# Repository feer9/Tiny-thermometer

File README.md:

# Tiny-thermomether

This project is mostly a recopilation of other projects I've found on various pages.  
I've just joined them at my personal taste, so I'll let the link to those projects below.  

## Parts used

+ ATtiny85
+ SSD1306 128x32 OLED I2C Display
+ DHT11 temperature and humidity sensor
+ DS18B20 water temperature sensor

## Electrical connection

ATtiny85  | PCB                   | Debug
--------- | --------------------- | --------
PB0       | Display SDA           | MOSI
PB1       | Push button           | MISO
PB2       | Display SCL           | CLK
PB3       | DHT11 (pin 2)         |
PB4       | DS18B20 (yellow wire) |
PB5       | N/C                   | RST

The sensors data lines have a 4.7K PullUp resistor.  
The push button have a 10K resistor.  
The I2C bus have a 10K PullUp resistor, both in SDA and SCL.

## Compilation and flashing

I've only tested it with avr-gcc on linux.  
To compile you need `avr-gcc` and `avr-g++`.  
To flash it I've used `avrdude` with an `usbasp-clone` avr programmer from [this other project](https://github.com/feer9/FASTUSBasp) running on an STM32F407VET6.  
Running `make flash` will compile and flash the program, but the first time you can `make install` to flash the program and fuses to match the clock speed.  

## Code included in this project:

https://www.instructables.com/ATTiny85-connects-to-I2C-OLED-display-Great-Things/

https://github.com/Jacajack/avr-ds18b20

https://www.hackster.io/boyanov/tinudht-c-library-for-dht11-temperature-humidity-sensor-c492e9

## Other pages of utility:

https://github.com/lexus2k/ssd1306

https://aprendiendoarduino.wordpress.com/2016/11/14/bus-i2ctwi/

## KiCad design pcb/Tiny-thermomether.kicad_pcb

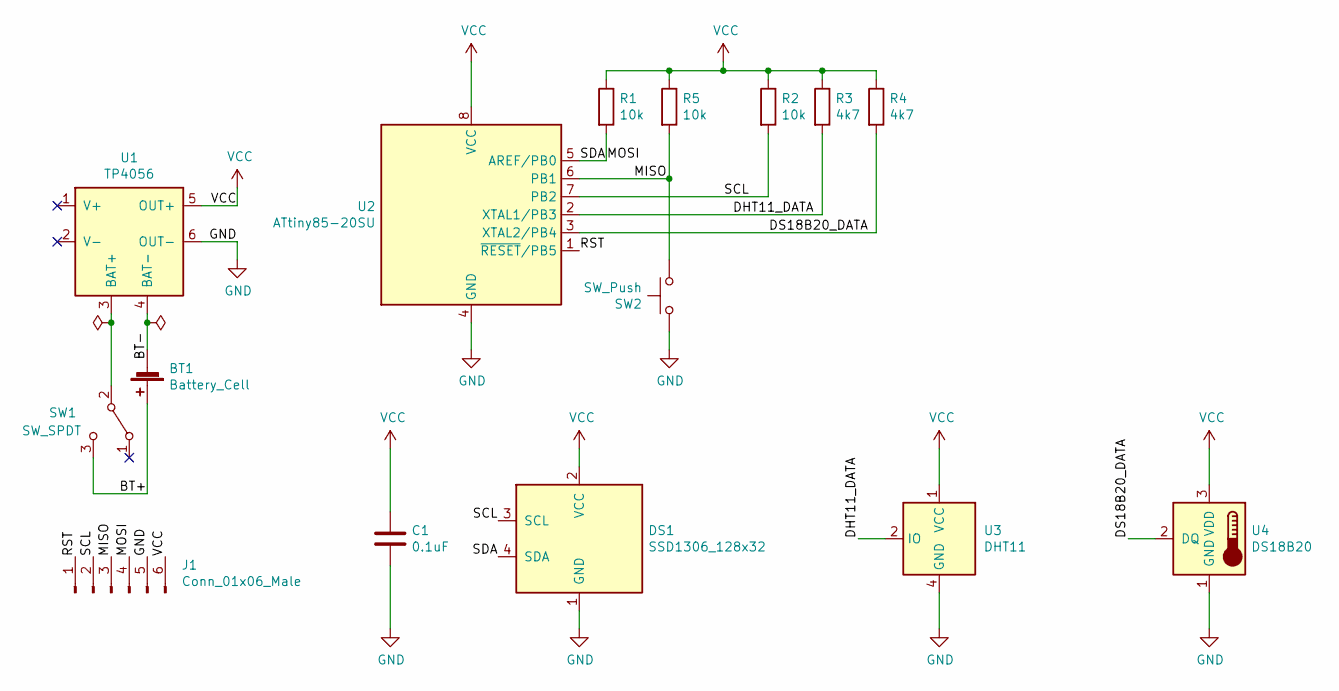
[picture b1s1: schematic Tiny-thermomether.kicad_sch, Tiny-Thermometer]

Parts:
BT1: Battery_Cell; JST_XH_S2B-XH-A_1x02_P2.50mm_Horizontal
C1: 0.1uF; C_1206_3216Metric_Pad1.33x1.80mm_HandSolder
DS1: SSD1306_128x32
J1: Conn_01x06_Male; PinHeader_1x06_P2.54mm_Horizontal
R1, R2, R5: 10k; R_1206_3216Metric_Pad1.30x1.75mm_HandSolder
R3, R4: 4k7; R_1206_3216Metric_Pad1.30x1.75mm_HandSolder
SW1: SW_SPDT; SW_SPDT_Angled_P3mm_13x5.5x6mm
SW2: SW_Push; SW_PUSH_6mm_H7.3mm
U1: TP4056
U2: ATtiny85-20SU; SOIJ-8_5.3x5.3mm_P1.27mm
U3: DHT11; Aosong_DHT11_5.5x12.0_P2.54mm_horizontal
U4: DS18B20; JST_XH_S3B-XH-A_1x03_P2.50mm_Horizontal

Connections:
/BT+: BT1.1 (+), SW1.3 (C)
/BT-: BT1.2 (-), U1.4 (BAT-)
/DHT11_DATA: R3.2, U2.2 (XTAL1/PB3), U3.2 (IO)
/DS18B20_DATA: R4.2, U2.3 (XTAL2/PB4), U4.2 (DQ)
/MISO: J1.3, R5.2, SW2.2, U2.6 (PB1)
/MOSI: DS1.4 (SDA), J1.4, R1.2, U2.5 (AREF/PB0)
/RST: J1.1, U2.1 (~RESET/PB5)
/SCL: DS1.3 (SCL), J1.2, R2.2, U2.7 (PB2)
GND: C1.2, DS1.1 (GND), J1.5, SW2.1, U1.6 (OUT-), U2.4 (GND), U3.4 (GND), U4.1 (GND); also elsewhere on the board
unnamed: SW1.2 (B), U1.3 (BAT+)
VCC: C1.1, DS1.2 (VCC), J1.6, R1.1, R2.1, R3.1, R4.1, R5.1, U1.5 (OUT+), U2.8 (VCC), U3.1 (VCC), U4.3 (VDD); also elsewhere on the board

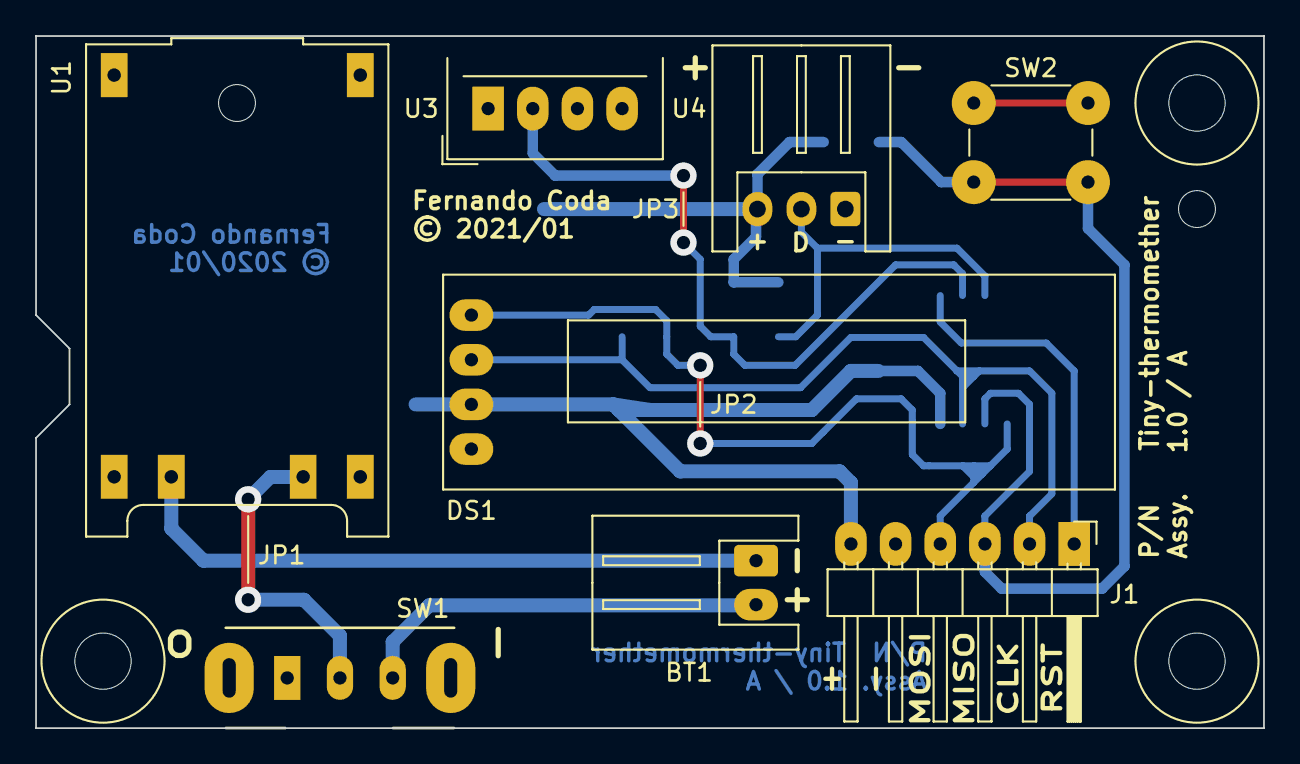
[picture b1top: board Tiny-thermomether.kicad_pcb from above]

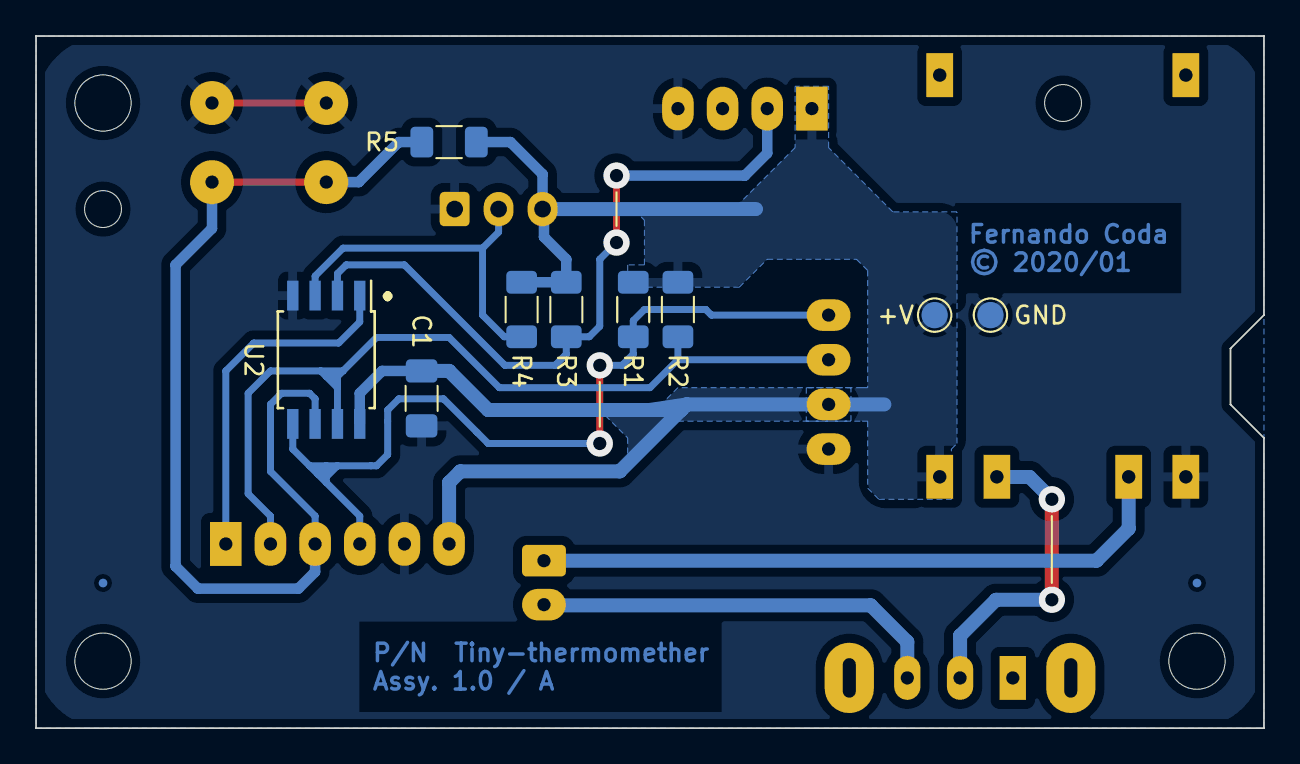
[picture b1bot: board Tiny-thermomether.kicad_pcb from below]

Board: 2 copper layers, 69.9 x 39.4 mm, 17 parts (9 on the bottom side), 11 nets.

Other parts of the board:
+V: TestPoint_Pad_D1.5mm
GND: TestPoint_Pad_D1.5mm

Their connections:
GND: GND.1; also elsewhere on the board
VCC: +V.1; also elsewhere on the board

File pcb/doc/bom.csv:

"Source:","/run/media/Datos/Feer/OneDrive - est.frba.utn.edu.ar/pcbs/attiny85/Tiny-thermomether/Tiny-thermomether.sch"
"Date:","sáb 13 mar 2021 17:37:19"
"Tool:","Eeschema 5.1.9"
"Generator:","/usr/share/kicad/plugins/bom_csv_grouped_by_value.py"
"Component Count:","15"

"Individual Components:"

"Item","Qty","Reference(s)","Value","LibPart","Footprint","Datasheet"
"","","BT1","Battery_Cell","Device:Battery_Cell","Connector_JST:JST_XH_S2B-XH-A_1x02_P2.50mm_Horizontal","~"
"","","C1","0.1uF","Device:C","Capacitor_SMD:C_1206_3216Metric_Pad1.33x1.80mm_HandSolder","~"
"","","DS1","SSD1306_128x32","ssd1306_128x32:SSD1306_128x32","ssd1306:SSD1306_128x32","https://www.digchip.com/datasheets/parts/datasheet/1121/AG-1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"
"","","J1","Conn_01x06_Male","Connector:Conn_01x06_Male","Connector_PinHeader_2.54mm:PinHeader_1x06_P2.54mm_Horizontal","~"
"","","R1","10k","Device:R","Resistor_SMD:R_1206_3216Metric_Pad1.30x1.75mm_HandSolder","~"
"","","R2","10k","Device:R","Resistor_SMD:R_1206_3216Metric_Pad1.30x1.75mm_HandSolder","~"
"","","R3","4k7","Device:R","Resistor_SMD:R_1206_3216Metric_Pad1.30x1.75mm_HandSolder","~"
"","","R4","4k7","Device:R","Resistor_SMD:R_1206_3216Metric_Pad1.30x1.75mm_HandSolder","~"
"","","R5","10k","Device:R","Resistor_SMD:R_1206_3216Metric_Pad1.30x1.75mm_HandSolder","~"
"","","SW1","SW_SPDT","Switch:SW_SPDT","Button_Switch_THT:SW_SPDT_Angled_P3mm_13x5.5x6mm","~"
"","","SW2","SW_Push","Switch:SW_Push","Button_Switch_THT:SW_PUSH_6mm_H7.3mm","~"
"","","U1","TP4056","tp4056:TP4056","tp4056:TP4056",""
"","","U2","ATtiny85-20SU","MCU_Microchip_ATtiny:ATtiny85-20SU","Package_SO:SOIJ-8_5.3x5.3mm_P1.27mm","http://ww1.microchip.com/downloads/en/DeviceDoc/atmel-2586-a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"
"","","U3","DHT11","Sensor:DHT11","Sensor:Aosong_DHT11_5.5x12.0_P2.54mm_horizontal","http://akizukidenshi.com/download/ds/aosong/DHT11.pdf"
"","","U4","DS18B20","Sensor_Temperature:DS18B20","Connector_JST:JST_XH_S3B-XH-A_1x03_P2.50mm_Horizontal","http://datasheets.maximintegrated.com/en/ds/DS18B20.pdf"



"Collated Components:"

"Item","Qty","Reference(s)","Value","LibPart","Footprint","Datasheet"
"1","1","BT1","Battery_Cell","Device:Battery_Cell","Connector_JST:JST_XH_S2B-XH-A_1x02_P2.50mm_Horizontal","~"
"2","1","C1","0.1uF","Device:C","Capacitor_SMD:C_1206_3216Metric_Pad1.33x1.80mm_HandSolder","~"
"3","1","DS1","SSD1306_128x32","ssd1306_128x32:SSD1306_128x32","ssd1306:SSD1306_128x32","https://www.digchip.com/datasheets/parts/datasheet/1121/AG-1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"
"4","1","J1","Conn_01x06_Male","Connector:Conn_01x06_Male","Connector_PinHeader_2.54mm:PinHeader_1x06_P2.54mm_Horizontal","~"
"5","3","R1, R2, R5","10k","Device:R","Resistor_SMD:R_1206_3216Metric_Pad1.30x1.75mm_HandSolder","~"
"6","2","R3, R4","4k7","Device:R","Resistor_SMD:R_1206_3216Metric_Pad1.30x1.75mm_HandSolder","~"
"7","1","SW1","SW_SPDT","Switch:SW_SPDT","Button_Switch_THT:SW_SPDT_Angled_P3mm_13x5.5x6mm","~"
"8","1","SW2","SW_Push","Switch:SW_Push","Button_Switch_THT:SW_PUSH_6mm_H7.3mm","~"
"9","1","U1","TP4056","tp4056:TP4056","tp4056:TP4056",""
"10","1","U2","ATtiny85-20SU","MCU_Microchip_ATtiny:ATtiny85-20SU","Package_SO:SOIJ-8_5.3x5.3mm_P1.27mm","http://ww1.microchip.com/downloads/en/DeviceDoc/atmel-2586-a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"
"11","1","U3","DHT11","Sensor:DHT11","Sensor:Aosong_DHT11_5.5x12.0_P2.54mm_horizontal","http://akizukidenshi.com/download/ds/aosong/DHT11.pdf"
"12","1","U4","DS18B20","Sensor_Temperature:DS18B20","Connector_JST:JST_XH_S3B-XH-A_1x03_P2.50mm_Horizontal","http://datasheets.maximintegrated.com/en/ds/DS18B20.pdf"

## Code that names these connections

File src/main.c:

#include "app.h"
#include <avr/wdt.h>

static void readButton(void);
static void endLoop(void);

/* Attiny85 PINS:

PB0: MOSI SDA
PB1: MISO
PB2:      SCL
PB3: 
PB4: 
PB5: Reset
*/

// TODO: ensure lowest frequency to reduce consumption
//       can't get too low since the display doesn't appear to like it

//__attribute__ ((address (0x1234)))

static uint32_t last_activity = 0;



static void endLoop(void)
{
	uint32_t T_inactive = (get_tick()-last_activity);
	uint8_t sleepmode;

	if(T_inactive <= LONG_PRESS_TIME)
		return;
	
	if(getScreenState() == SCREEN_OFF && T_inactive > 5000) {
		// Sleep until an external interrupt
		sleepmode = SLEEP_MODE_PWR_DOWN;
	}
	else if(T_inactive > 1000*60*5) {
		// Turn screen OFF and sleep until an external interrupt
		screenOFF();
		sleepmode = SLEEP_MODE_PWR_DOWN;
	}
	else {
		// Sleep until a timer interrupt
		sleepmode = SLEEP_MODE_IDLE;
	}
	
	cli();
	set_sleep_mode(sleepmode);
	sleep_enable();
	if (sleepmode == SLEEP_MODE_PWR_DOWN)
		sleep_bod_disable();
	sei();
	sleep_cpu();
	sleep_disable();
}

// Basic debounce function based on an Arduino example
static void readButton(void)
{
	static uint8_t button_st = BUTTON_RELEASED;
	static uint8_t last_reading = BUTTON_RELEASED;
	static uint32_t T_last_change = 0; // time in which the last state change happened
	static bool longpressed = false;
	uint32_t elapsed;                  // time elapsed since last state change
	uint8_t curr_reading = pin_get(BUTTON_PIN);
	const uint32_t curr_tick = get_tick();

	// If the switch changed, due to noise or pressing:
	if(curr_reading != last_reading) {
		// reset the debouncing timer
		T_last_change = curr_tick;
	}

	elapsed = curr_tick-T_last_change;
	if(elapsed > DEBOUNCE_DELAY)
	{
		// whatever the reading is at, it's been there for longer than
		// the debounce delay, so take it as the actual current state:

		// if the button state has changed:
		if(curr_reading != button_st)
		{	
			button_st = curr_reading;
			last_activity = curr_tick;

			if(curr_reading == BUTTON_RELEASED && elapsed < LONG_PRESS_TIME && !longpressed) {
				buttonSimpleAction();
			}

			longpressed   = false;
		}
		else if(curr_reading == BUTTON_PRESSED && !longpressed && elapsed >= LONG_PRESS_TIME)
		{
			longpressed = true;
			buttonLongPressed();
		}
	}

	last_reading = curr_reading;
}

ISR(PCINT0_vect)
{
	last_activity = get_tick();
}

static void enable_interrupts(void)
{
	// Turn on external interrupts on BUTTON_PIN
	//  BUTTON_PIN = PB1 = PCINT1

	// Set Pin Change Interrupt Enable on General Interrupt Mask Register
	GIMSK = (1 << PCIE);
	// Enable Pin Change Interrupt on PB1
	PCMSK |= (1 << PCINT1);

	// Enable Global Interrupt
	sei();
}

static void GPIO_init(void)
{
	pinmode_input(BUTTON_PIN);
	pinmode_pullup_off(BUTTON_PIN);
}

static void WDT_off(void)
{
	wdt_reset();
	/* Clear WDRF in MCUSR */
	MCUSR = 0x00;
	/* Write logical one to WDCE and WDE */
	WDTCR |= (1<<WDCE) | (1<<WDE);
	/* Turn off WDT */
	WDTCR = 0x00;
}

static void power_management(void)
{
	// Turn off Analog Comparator
	ACSR = (1 << ACD);
	// Shut down Timer1 and ADC
	PRR  = (1 << PRTIM1) | (1 << PRADC);

	// Turn off Watch Dog Timer
	WDT_off();
}

void uC_init(void)
{
	GPIO_init();

	// Stop interrupts
    cli();

	Timer0_init();

	power_management();

	enable_interrupts();

	appSetup();
}

void main (void)
{
	uC_init();

	for(;;) {
		readButton();

		appLoop();

		endLoop();
	}
}

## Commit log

2020-12-30 Rename readme.md to README.md
2020-12-31 Change screen update time logic
2021-01-05 New features and bugfixes
    Fixed a bug in the way float number are converted to string
    Added a "float" class for better number manipulation
2021-01-05 Add some basic power management
2021-01-05 Reduced 10% of flash usage porting all code to C
2021-01-09 Use many avr-gcc optimizations
2021-01-09 Restructured oled driver to accept variable font sizes
    Added 8x16, 12x16 and 24x32 fonts
    Optimized i2c write routine on the display side
2021-01-09 Restructured main()
    I have separated routines in simple functions
    Divided the display into 2 screens,
    one for the ds18b20 and the other for the dht11 sensor.
    This way I can use a bigger font.
    Each screen also has new bitmaps.
    In the future, screen switch will be managed by a button instead of a timer.
2021-01-09 Add compiled files (and tiny bugfix)
2022-01-02 Replace the LED with a push button Added some basic functionallity for it to change screens instead of a timed sequence
2022-01-03 Set the push button as an external interrupt
2022-01-03 Added on() and off() functions to ssd1306
2022-01-04 Restructured main.c Move some display and sensors code to "app.c"
2022-01-04 Simplified DS18B20 library
2022-01-04 Added init function
2022-01-04 Fix a button reading bug
2022-01-04 Put to sleep after 1 minute of inactivity
2022-01-04 Update binary files
2022-01-05 Add 8ms and 50ms tickrates for SysTick interrupts. Default to 8ms. Couldn't get 50ms to work in 8MHz sysclock.
2022-01-05 Minor bugfix to screen drawing
2022-01-05 Add 2.7V Brown-Out Detection in 1 and 8 MHz fuses
2022-01-05 Minor improvements in power management and button actions
2022-01-05 Reorganize and cleanup
2022-01-06 Fixed BOD-disable at sleep sequence. Fixed power-down sleep issue.
2022-01-06 Add PCB and Case to Git
2022-01-06 Add image to README.md
2022-09-10 Add check option, update defaults
2022-09-10 Add build and run tasks
2022-09-10 Add battery module documentation reference
2022-09-10 Rename, refactor and order
2022-09-10 Rewrite DHT11 library
2022-09-10 Improve fixed point decimal manipulation fix/improve decimals representation in oled display also fix negative values in sensor reading
2022-09-10 update gitignore
2022-09-10 update binaries

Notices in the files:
pcb/Tiny-thermomether.kicad_pcb:
© 2020/01
© 2021/01
